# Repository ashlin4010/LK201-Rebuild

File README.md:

# LK201-Rebuild

> Note: This  project only 50% complete and 100% untested.

This project is to replace the membrane inside of a LK201 VT220 keyboard.

Doing so it destructive and not reversible however if the alternative is a non-functional keyboard...

## Remaining work to complete
* PCB revision 2
    * Move some key rows down by about 0.5mm
    * Improvement mechanical fitment
    * Mounting holes
    * Insulating layer/drill guide
    * Keycap Inserts

## Fabrication
When getting the PCB fabricated you can split them into parts. This may or may not save cost.

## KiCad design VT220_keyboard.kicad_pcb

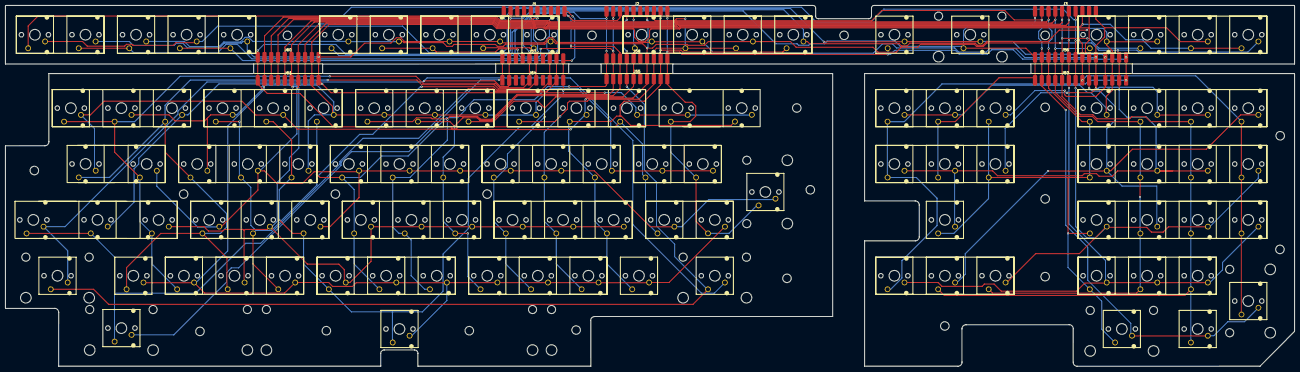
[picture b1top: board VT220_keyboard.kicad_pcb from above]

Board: 2 copper layers, 484.4 x 135.6 mm, 89 parts (0 on the bottom side), 26 nets.

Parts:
H4, H5, H6, H7, H8, H9, H10, H11, H12, H13, H14, H15, H16, H17, H18, H19, H20, H21: MountingHole_3.2mm_M3
J1, J2, J3, J54, J55, J56, J57, J58, J59, J60, J61: Conn_01x10_Pin; rectangle_pad_10
J10, J12, J27, J32: SW_MX_2
J11, J13, J18, J19, J20, J21, J24, J25, J26, J29, J30, J31, J35, J36, J37, J43, J44, J46, J50: SW_MX_3
J14, J17, J47, J48, J49: SW_MX_4
J15, J16, J33, J34, J38, J39, J40, J41, J42, J45, J51, J52, J53: SW_MX_1
J22, J23, J28: SW_MX_3_LONG
J62, J63, J64, J65, J66, J67, J68, J69: Conn_01x01_Pin; rectangle_pad
M1, M2, M3, M6, M7, M8: STAB_MX_2u
M4: STAB_MX_7u
M5: STAB_MX_6.25u

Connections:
1: J1.1, J15.2, J16.2, J41.2, J43.6, J54.1, J57.1, J62.1, J66.1
2: J1.2, J10.2, J11.4, J14.8, J17.2, J17.4, J28.2, J33.2, J39.2, J43.2, J43.4, J47.2, J54.2, J57.2, J63.1, J67.1
3: J1.5, J18.1, J18.3, J23.3, J28.5, J35.1, J54.5, J57.5
4: J1.6, J10.1, J18.5, J23.1, J24.1, J29.1, J34.1, J35.3, J54.6, J57.6
5: J1.8, J10.3, J11.1, J19.1, J24.3, J29.3, J35.5, J54.8, J57.8
6: J1.9, J28.1, J28.3, J41.1, J54.9, J57.9
7: J1.10, J11.3, J11.5, J19.3, J24.5, J29.5, J36.1, J42.1, J54.10, J57.10
8: J2.1, J12.1, J19.5, J25.1, J30.1, J36.3, J55.1, J58.1
9: J2.2, J12.3, J13.1, J20.1, J25.3, J30.3, J36.5, J55.2, J58.2
10: J2.3, J13.3, J13.5, J20.3, J25.5, J30.5, J37.1, J55.3, J58.3
11: J2.4, J33.1, J39.1, J55.4, J58.4
12: J2.5, J14.1, J20.5, J26.1, J31.1, J37.3, J55.5, J58.5
13: J2.7, J11.2, J12.2, J12.4, J13.6, J14.6, J17.8, J18.2, J19.4, J21.4, J23.2, J44.2, J44.4, J45.2, J48.4, J48.6, J55.7, J58.7, J64.1, J68.1
14: J2.8, J14.3, J14.5, J21.1, J26.3, J31.3, J37.5, J55.8, J58.8
15: J2.9, J14.7, J21.3, J22.3, J26.5, J31.5, J38.1, J55.9, J58.9
16: J2.10, J15.1, J22.1, J27.3, J32.3, J40.1, J43.1, J44.1, J46.1, J55.10, J58.10, J65.1, J69.1
17: J3.1, J16.1, J21.5, J27.1, J32.1, J43.3, J44.3, J56.1, J59.1, J60.1, J61.1
18: J3.2, J32.4, J34.2, J35.2, J35.6, J36.4, J36.6, J37.2, J37.4, J37.6, J38.2, J42.2, J51.2, J52.2, J53.2, J56.2, J59.2, J60.2, J61.2
19: J3.3, J43.5, J44.5, J45.1, J47.1, J48.1, J49.1, J50.1, J51.1, J56.3, J59.3, J60.3, J61.3
20: J3.4, J17.1, J46.5, J47.3, J48.3, J49.3, J50.3, J56.4, J59.4, J60.4, J61.4
21: J3.5, J17.3, J46.3, J47.5, J48.5, J49.5, J50.5, J52.1, J56.5, J59.5, J60.5, J61.5
22: J3.6, J28.6, J29.4, J30.2, J30.4, J30.6, J31.2, J31.4, J31.6, J35.4, J36.2, J46.2, J49.8, J50.2, J50.4, J50.6, J56.6, J59.6, J60.6, J61.6
23: J3.7, J23.4, J24.4, J25.2, J25.4, J25.6, J26.2, J26.4, J29.2, J29.6, J32.2, J40.2, J46.6, J48.8, J49.2, J49.6, J56.7, J59.7, J60.7, J61.7
24: J3.8, J17.5, J17.7, J47.7, J48.7, J49.7, J53.1, J56.8, J59.8, J60.8, J61.8
25: J3.9, J18.4, J19.2, J19.6, J20.2, J20.4, J20.6, J21.2, J24.2, J24.6, J26.6, J27.2, J27.4, J46.4, J47.8, J48.2, J49.4, J56.9, J59.9, J60.9, J61.9
26: J3.10, J10.2, J11.6, J13.2, J13.4, J14.2, J14.4, J17.6, J18.6, J21.6, J22.2, J22.4, J28.4, J44.6, J47.4, J47.6, J56.10, J59.10, J60.10, J61.10

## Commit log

2025-04-18 Back up project
2025-04-19 Update PCB
